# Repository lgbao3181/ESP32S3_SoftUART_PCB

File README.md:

# Dự án ESP32S3_Distance_SoftUART

## Giới thiệu

Đây là một dự án Embedded Systems tập trung vào việc **tự xây dựng Software UART (bit-banging) trên ESP32-S3**, kết hợp với quá trình **thiết kế sơ đồ nguyên lý (Schematic) và mạch in PCB**.

Thay vì sử dụng trực tiếp UART peripheral có sẵn của ESP32-S3 cho kênh giao tiếp với PC, dự án tự điều khiển GPIO bằng phần mềm để thực hiện quá trình truyền và nhận dữ liệu UART ở mức bit. Firmware chịu trách nhiệm xử lý timing, Start bit, Data bits và Stop bit của khung UART.

Bên cạnh phần firmware, dự án thực hiện quá trình thiết kế phần cứng từ **Schematic đến PCB**, bao gồm lựa chọn linh kiện, cấu hình chân, bố trí linh kiện, routing và kiểm tra thiết kế.

ESP32-S3 sử dụng **UART phần cứng** để giao tiếp với cảm biến siêu âm US-100, đồng thời sử dụng **Software UART** trên GPIO43/GPIO44 để giao tiếp với PC thông qua bộ chuyển đổi USB–UART.

Dữ liệu khoảng cách được đóng gói theo một định dạng khung tự định nghĩa và sử dụng **CRC16 (Modbus)** để kiểm tra lỗi trong quá trình truyền.

Ứng dụng **C# WinForms** được sử dụng làm giao diện phía PC để giám sát và trao đổi dữ liệu với ESP32-S3.

---

## Video minh họa

https://github.com/user-attachments/assets/1926875d-f966-454c-846d-3aac775d518c

---

## Sơ đồ nguyên lý

Sơ đồ trên thể hiện hai tuyến giao tiếp UART độc lập trên ESP32-S3:

* **UART mềm (Software UART)**: GPIO43/GPIO44 ↔ USB–UART Converter ↔ PC. Đây là tuyến được tự xây dựng bằng phương pháp **bit-banging**.
* **UART phần cứng (Hardware UART)**: GPIO17/GPIO18 ↔ US-100. Tuyến này sử dụng peripheral UART có sẵn của ESP32-S3.

---

## Sơ đồ mạch in (PCB)

PCB được thiết kế dựa trên sơ đồ nguyên lý nhằm thể hiện quá trình chuyển từ thiết kế mạch điện sang bố trí mạch in.

Thiết kế bao gồm:

* Bố trí module ESP32-S3.
* Đầu nối cho US-100.
* Đầu nối cho USB–UART Converter.
* Routing các đường tín hiệu.
* Kết nối nguồn và GND.
* Kiểm tra kết nối giữa Schematic và PCB.

> Hình ảnh PCB trong thư mục `demo` dùng để minh họa thiết kế và bố trí mạch, không phải file Gerber sản xuất.

---

---
## Nguyên mẫu hoàn thiện
---
## Thành phần phần cứng

| Thành phần              | Số lượng | Vai trò                                                   |
| ----------------------- | -------: | --------------------------------------------------------- |
| ESP32-S3                |        1 | MCU trung tâm, chạy firmware và Software UART             |
| Cảm biến siêu âm US-100 |        1 | Đo khoảng cách, giao tiếp với ESP32-S3 qua UART phần cứng |
| Bộ chuyển đổi USB–UART  |        1 | Cầu nối giữa Software UART của ESP32-S3 và PC             |
| PC / Laptop             |        1 | Chạy ứng dụng WinForms để giám sát và giao tiếp           |

---

## Cấu hình chân

### US-100 – ESP32-S3 (UART phần cứng)

| Chân ESP32-S3 | Chức năng | Chân US-100 | Ghi chú                                   |
| ------------- | --------- | ----------- | ----------------------------------------- |
| **GPIO17**    | UART RX   | **TX**      | ESP32-S3 nhận dữ liệu từ US-100           |
| **GPIO18**    | UART TX   | **RX**      | ESP32-S3 gửi lệnh tới US-100              |
| **GND**       | Mass      | **GND**     | **Bắt buộc phải nối chung**               |
| **5V / VCC**  | Nguồn     | **VCC**     | Cấp nguồn theo thông số của module US-100 |

### UART mềm – PC

| Chân ESP32-S3 | Chức năng        | USB–UART Converter | Mục đích                    |
| ------------- | ---------------- | ------------------ | --------------------------- |
| **GPIO43**    | Software UART TX | **RX**             | ESP32-S3 gửi dữ liệu lên PC |
| **GPIO44**    | Software UART RX | **TX**             | ESP32-S3 nhận dữ liệu từ PC |
| **GND**       | Mass             | **GND**            | **Bắt buộc phải nối chung** |

---

## Software UART tự xây dựng — phần trọng tâm của dự án

Do một kênh UART phần cứng được sử dụng để giao tiếp với US-100, dự án tự xây dựng một **Software UART (bit-banging)** trên GPIO43/GPIO44 để tạo thêm một kênh giao tiếp độc lập với PC.

Mục tiêu của phần này là thực hành và hiểu nguyên lý hoạt động của UART ở mức bit, thay vì chỉ sử dụng peripheral UART hoặc thư viện có sẵn.

### 1. Nguyên lý bit-banging

Software UART không sử dụng bộ ngoại vi UART chuyên dụng của ESP32-S3. Thay vào đó, firmware trực tiếp điều khiển mức logic HIGH/LOW trên GPIO theo timing của từng bit.

* **TX (phát)**: GPIO được cấu hình Output và thay đổi mức logic theo từng bit của khung UART.
* **RX (thu)**: GPIO được cấu hình Input và lấy mẫu tín hiệu tại các thời điểm xác định để xác định giá trị của từng bit.

### 2. Thông số khung truyền

* Tốc độ baud: **9600 bps**
* Định dạng: **8N1**

  * 8 bit dữ liệu
  * Không Parity
  * 1 Stop bit
* *Bit time*:

```text
Tbit = 1 / 9600
     ≈ 104 µs
```

*Bit time* là khoảng thời gian của một bit. Việc đảm bảo timing chính xác là yếu tố quan trọng để Software UART có thể truyền và nhận dữ liệu ổn định.

### 3. Quy trình phát (TX) do phần mềm điều khiển

1. Đưa đường truyền về trạng thái Idle HIGH.
2. Kéo GPIO xuống LOW trong một *bit time* để tạo **Start bit**.
3. Lần lượt truyền 8 bit dữ liệu.
4. Mỗi bit được giữ trong một *bit time*.
5. Đưa GPIO lên HIGH để tạo **Stop bit**.
6. Đường truyền trở về trạng thái Idle.

### 4. Quy trình thu (RX) do phần mềm điều khiển

1. Theo dõi GPIO ở trạng thái Idle HIGH.
2. Phát hiện cạnh xuống để xác định **Start bit**.
3. Chờ khoảng nửa *bit time* để lấy mẫu tại giữa Start bit.
4. Tiếp tục lấy mẫu mỗi *bit time* để nhận 8 bit dữ liệu.
5. Ghép các bit đã nhận thành một byte.
6. Kiểm tra **Stop bit**.
7. Nếu Stop bit không hợp lệ, dữ liệu được xem là lỗi khung (**Frame Error**).

### 5. Định dạng gói tin và CRC16

Sau khi Software UART truyền và nhận được các byte dữ liệu, firmware đóng gói dữ liệu khoảng cách theo định dạng:

```text
@DATA:CRC&
```

Trong đó:

* `@` — Ký tự bắt đầu khung.
* `DATA` — Giá trị khoảng cách.
* `:` — Ký tự phân cách.
* `CRC` — Mã kiểm tra **CRC16 (Modbus)**.
* `&` — Ký tự kết thúc khung.

CRC16 được tính trên phần `DATA`.

Bên nhận sẽ tính lại CRC16 và so sánh với giá trị CRC nhận được:

```text
DATA
  │
  ▼
Tính CRC16
  │
  ▼
@DATA:CRC&
  │
  ▼
Software UART
  │
  ▼
Nhận dữ liệu
  │
  ▼
Kiểm tra CRC
  │
  ├── Hợp lệ   → Chấp nhận dữ liệu
  │
  └── Không hợp lệ → CRC_FAIL
```

### 6. So sánh UART phần cứng và Software UART

| Tiêu chí            | UART phần cứng                     | Software UART            |
| ------------------- | ---------------------------------- | ------------------------ |
| Bộ điều khiển       | Peripheral UART tích hợp trong MCU | Phần mềm điều khiển GPIO |
| Timing              | Được phần cứng xử lý               | Phụ thuộc vào firmware   |
| Tải CPU             | Thấp                               | Cao hơn                  |
| Độ phụ thuộc timing | Thấp                               | Cao                      |
| Trong dự án         | Giao tiếp với US-100               | Giao tiếp với PC         |

---

## Kiến trúc hệ thống tổng quan

```text
┌──────────────────────┐
│    Ứng dụng WinForms │
│     (PC / Laptop)    │
└──────────┬───────────┘
           │
           │ Software UART
           │ @DATA:CRC&
           ▼
┌──────────────────────┐
│       ESP32-S3       │
│                      │
│ ┌──────────────────┐ │
│ │  Software UART   │ │
│ │     + CRC16      │ │
│ └────────┬─────────┘ │
│          │           │
│ ┌────────▼─────────┐ │
│ │  UART phần cứng  │ │
│ └────────┬─────────┘ │
└──────────┼───────────┘
           │
           │ UART
           ▼
┌──────────────────────┐
│        US-100        │
│    Cảm biến siêu âm  │
└──────────────────────┘
```

### Quy trình hoạt động

1. **Khởi tạo:** cấu hình UART phần cứng cho US-100 và Software UART trên GPIO43/GPIO44.
2. **Đo khoảng cách:** ESP32-S3 gửi lệnh `0x55` tới US-100 và đọc dữ liệu phản hồi.
3. **Đóng gói dữ liệu:** tính CRC16 (Modbus) và tạo khung `@DATA:CRC&`.
4. **Truyền dữ liệu:** ESP32-S3 gửi khung dữ liệu lên PC thông qua Software UART.
5. **Giao tiếp với PC:** WinForms nhận, phân tích và hiển thị dữ liệu.
6. **Kiểm tra lỗi:** dữ liệu nhận được được kiểm tra CRC trước khi chấp nhận.

---

## Bắt đầu

### Yêu cầu phần mềm

| Phần mềm                 | Phiên bản | Mục đích                                |
| ------------------------ | --------- | --------------------------------------- |
| Arduino IDE / PlatformIO | Mới nhất  | Phát triển và nạp firmware cho ESP32-S3 |
| ESP32 Arduino Core       | Mới nhất  | Hỗ trợ ESP32-S3                         |
| C# / .NET WinForms       | .NET 6+   | Ứng dụng phía PC                        |
| Serial Terminal          | Bất kỳ    | Kiểm thử và gỡ lỗi UART                 |

### Lắp phần cứng

* Nối US-100 với **GPIO17 (RX)** và **GPIO18 (TX)**.
* Nối USB–UART Converter với **GPIO43 (TX)** và **GPIO44 (RX)**.
* Nối chung **GND** giữa ESP32-S3, US-100 và USB–UART Converter.
* Đảm bảo mức điện áp logic của USB–UART Converter tương thích với ESP32-S3.
* Cấp nguồn phù hợp cho US-100.

### Cài đặt

1. Sao chép repository:

```bash
git clone <repository-url>
cd ESP32S3_Distance_SoftUART
```

2. Mở thư mục firmware bằng **Arduino IDE hoặc PlatformIO**.

3. Chọn đúng board **ESP32-S3**.

4. Chọn đúng cổng serial của ESP32-S3.

5. Biên dịch và nạp firmware.

6. Kết nối USB–UART Converter với PC.

7. Mở ứng dụng WinForms hoặc Serial Terminal để kiểm tra dữ liệu.

8. Khởi động hệ thống. ESP32-S3 sẽ đọc dữ liệu từ US-100 và truyền dữ liệu lên PC thông qua Software UART.

### Kiểm thử giao tiếp

Có thể sử dụng Serial Terminal hoặc ứng dụng WinForms để kiểm tra Software UART.

Các nội dung cần kiểm tra:

* Baud rate **9600 bps**.
* Khung UART **8N1**.
* Dữ liệu TX/RX.
* Định dạng `@DATA:CRC&`.
* Kiểm tra CRC16.
* Phát hiện Frame Error.
* Giao tiếp giữa ESP32-S3 và PC.

---

## Tài liệu tham khảo

* [Datasheet ESP32-S3](https://www.espressif.com/sites/default/files/documentation/esp32-s3_datasheet_en.pdf)
* [Tài liệu tham chiếu kỹ thuật ESP32-S3](https://www.espressif.com/sites/default/files/documentation/esp32-s3_technical_reference_manual_en.pdf)
* [Tài liệu Arduino-ESP32](https://docs.espressif.com/projects/arduino-esp32/en/latest/)
* [Datasheet cảm biến siêu âm US-100](https://www.mouser.com/datasheet/2/813/US-100-DS-1218130.pdf)
* [Tài liệu Microsoft .NET](https://learn.microsoft.com/en-us/dotnet/)
* [Tài liệu Windows Forms](https://learn.microsoft.com/en-us/dotnet/desktop/winforms/)
* [CRC16 Modbus](https://www.modbustools.com/modbus_crc16.htm)

---

## Trạng thái dự án

* **Trạng thái:** Hoàn thành
* **Phiên bản:** v1.0
* **Cập nhật lần cuối:** Tháng 9/2026

---

## Liên hệ

**Gia Bảo**

📧 Email: *[your-email@example.com](mailto:your-email@example.com)*
🐙 GitHub: *your-github-profile*

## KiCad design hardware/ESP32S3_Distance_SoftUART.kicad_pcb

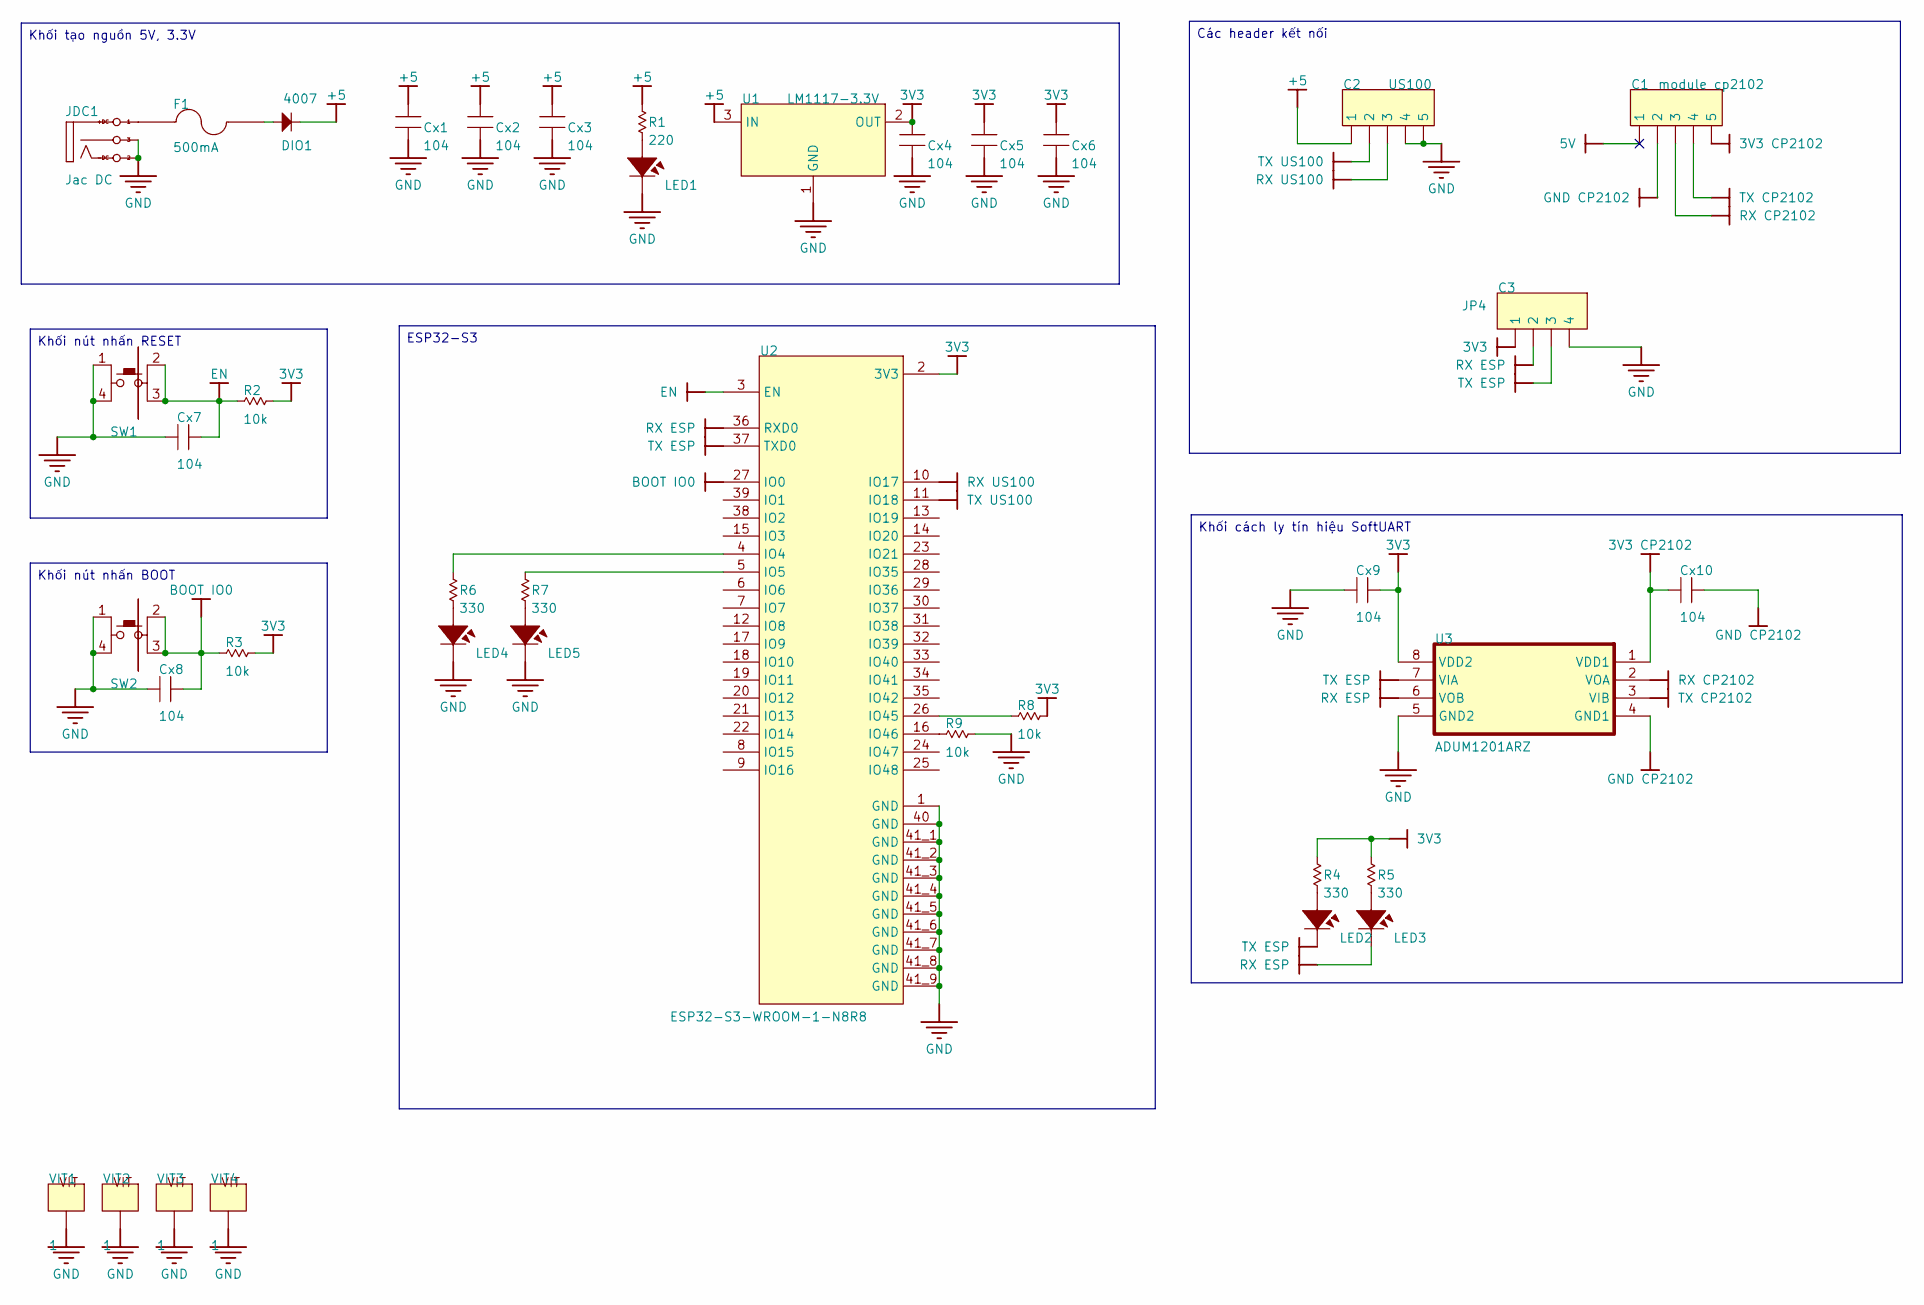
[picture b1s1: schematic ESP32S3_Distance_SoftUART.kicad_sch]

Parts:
C1: module cp2102; Header5; PARTNO 613002143121
C2: US100; Header5; PARTNO 613002143121
C3: JP4; JP4-C1T; PARTNO 613004143121
Cx1, Cx2, Cx3, Cx4, Cx5, Cx6, Cx7, Cx8, Cx9, Cx10: 104; CN-SMD-0805
DIO1: 4007; DIO-SMD-106
F1: Fuse; FUSE_0805; PARTNUMBER MF-PSMF050X-2
JDC1: Jac DC; DC0
LED1, LED2, LED3, LED4, LED5: LED; LED-0805-Yellow
R1: 220; RES-SMD-0805
R2, R3, R8, R9: 10k; RES-SMD-0805
R4, R5, R6, R7: 330; RES-SMD-0805
SW1: RESET; SWPBS_SPDT_6X6X5
SW2: BOOT; SWPBS_SPDT_6X6X5
U1: LM1117-3.3V; SOT223
U2: ESP32-S3-WROOM-1-N8R8; XCVR_ESP32S3WROOM1N8R8
U3: ADUM1201ARZ; SOIC127P600X175-8N
VIT1, VIT2, VIT3, VIT4: 1; VIT

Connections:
3V3: C3.1, Cx4.2, Cx5.2, Cx6.2, Cx9.1, R2.1, R3.1, R4.1, R5.1, R8.1, U1.2 (OUT), U2.2 (3V3), U3.8 (VDD2)
3V3 CP2102: C1.5, Cx10.2, U3.1 (VDD1)
5V: C1.1
+5: C2.1, Cx1.2, Cx2.2, Cx3.2, DIO1.2 (K), R1.1, U1.3 (IN)
BOOT IO0: Cx8.1, R3.2, SW2.2 (P3), SW2.3 (P4), U2.27 (IO0)
EN: Cx7.1, R2.2, SW1.2 (P3), SW1.3 (P4), U2.3 (EN)
GND: C2.4, C2.5, C3.4, Cx1.1, Cx2.1, Cx3.1, Cx4.1, Cx5.1, Cx6.1, Cx7.2, Cx8.2, Cx9.2, JDC1.2 (TN), JDC1.3 (S), LED1.2, LED4.2, LED5.2, R9.1, SW1.1, SW1.4 (P2), SW2.1, SW2.4 (P2), U1.1 (GND), U2.1 (GND), U2.40 (GND), U2.41_1 (GND), U2.41_2 (GND), U2.41_3 (GND), U2.41_4 (GND), U2.41_5 (GND), U2.41_6 (GND), U2.41_7 (GND), U2.41_8 (GND), U2.41_9 (GND), U2.41_10, U2.41_11, U2.41_12, U2.41_13, U2.41_14, U2.41_15, U2.41_16, U2.41_17, U2.41_18, U2.41_19, U2.41_20, U2.41_21, U3.5 (GND2), VIT1.VIT1, VIT2.VIT1, VIT3.VIT1, VIT4.VIT1
GND CP2102: C1.2, Cx10.1, U3.4 (GND1)
NetDIO1_1: DIO1.1 (A), F1.2
NetF1_1: F1.1, JDC1.1 (T)
NetLED1_1: LED1.1, R1.2
NetLED2_1: LED2.1, R4.2
NetLED3_1: LED3.1, R5.2
NetLED4_1: LED4.1, R6.2
NetLED5_1: LED5.1, R7.2
NetR6_1: R6.1, U2.4 (IO4)
NetR7_1: R7.1, U2.5 (IO5)
NetR8_2: R8.2, U2.26 (IO45)
NetR9_2: R9.2, U2.16 (IO46)
RX CP2102: C1.3, U3.2 (VOA)
RX ESP: C3.2, LED3.2, U2.36 (RXD0), U3.6 (VOB)
RX US100: C2.3, U2.10 (IO17)
TX CP2102: C1.4, U3.3 (VIB)
TX ESP: C3.3, LED2.2, U2.37 (TXD0), U3.7 (VIA)
TX US100: C2.2, U2.11 (IO18)

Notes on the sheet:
Khối nút nhấn RESET
Các header kết nối
Khối tạo nguồn 5V, 3.3V
ESP32-S3
Khối nút nhấn BOOT
Khối cách ly tín hiệu SoftUART

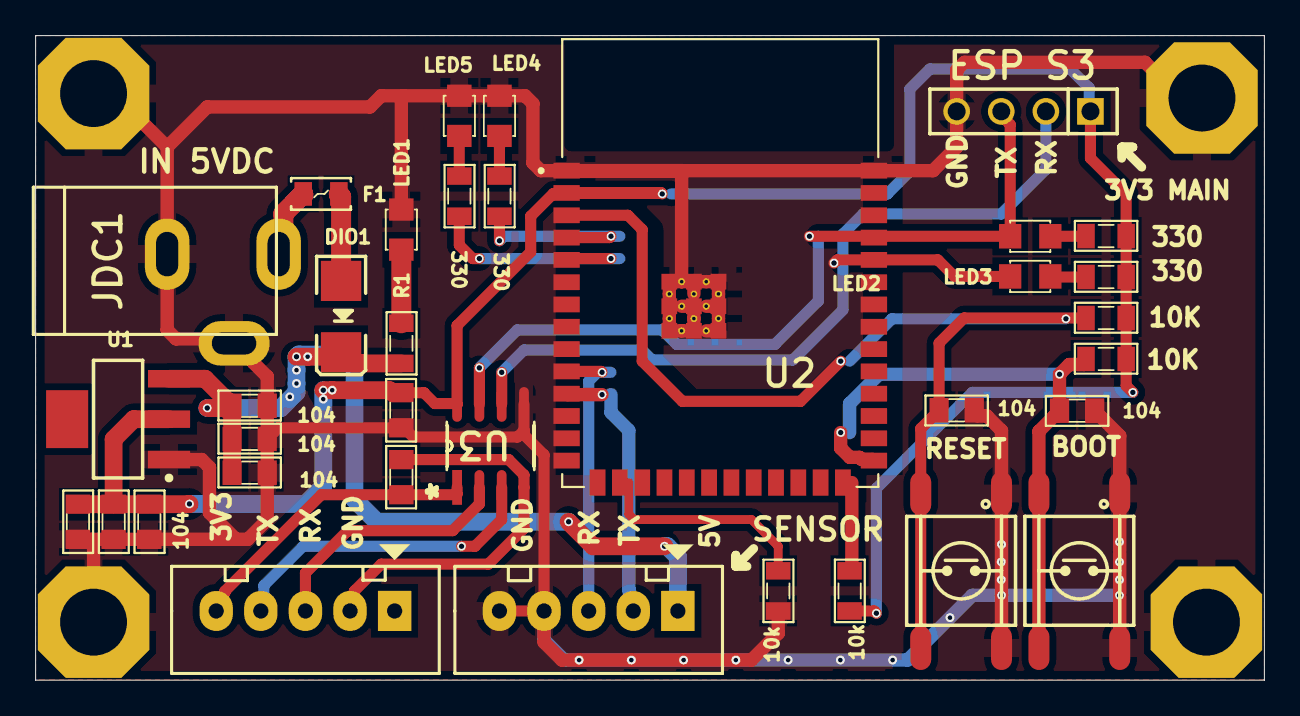
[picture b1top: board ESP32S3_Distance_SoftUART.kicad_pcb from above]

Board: 2 copper layers, 70.0 x 36.7 mm, 39 parts (0 on the bottom side), 24 nets.

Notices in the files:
README.md:
License: MIT
